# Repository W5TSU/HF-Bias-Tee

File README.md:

# HF Bias-Tee

Designed in KiCAD V9. 

This is my first attempt to design a board. I'll post some results after HF testing.

## References
- [Started as - https://github.com/zleffke/kicad_bias_tee](https://github.com/zleffke/kicad_bias_tee)
- [Reeve Observatory - Long Wavelength Array Active Crossed-Dipole Antenna](http://www.reeve.com/RadioScience/Antennas/ActiveCrossed-Dipole/LWA_Antenna.htm)
- [Long Wavelength Array (LWA) Memo Series](https://www.faculty.ece.vt.edu/swe/lwa/)
- [Bias-T Design Considerations for the LWA by Brian Hicks, Bill Erickson](https://www.faculty.ece.vt.edu/swe/lwa/memo/lwa0135.pdf)
# HF-Bias-Tee

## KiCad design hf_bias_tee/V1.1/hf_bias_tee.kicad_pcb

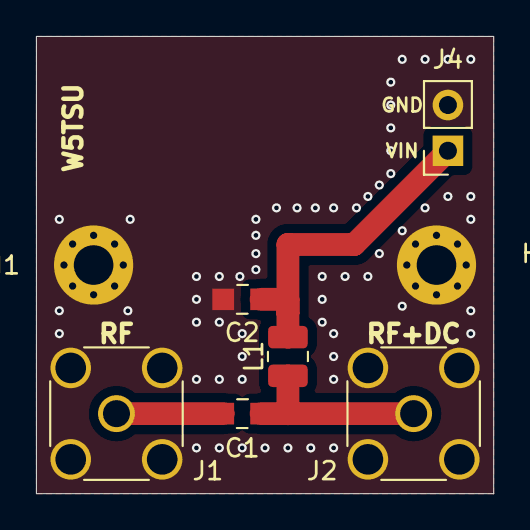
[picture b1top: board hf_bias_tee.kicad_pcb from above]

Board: 2 copper layers, 25.4 x 25.4 mm, 8 parts (0 on the bottom side), 4 nets.

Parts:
C1, C2: 0.1uF; 0805
H1, H2: MHP; MountingHole_2.2mm_M2_Pad_Via
J1: RF; SMA_Amphenol_132134_Vertical
J2: RF+DC; SMA_Amphenol_132134_Vertical
J4: DC; PinSocket_1x02_P2.54mm_Vertical
L1: 4.7uH; L_1008_2520Metric

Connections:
GND: C2.2, H1.1, H2.1, J1.2, J2.2, J4.2
unnamed: C1.1, J2.1, L1.2
unnamed: C1.2, J1.1
unnamed: C2.1, J4.1, L1.1

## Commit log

2025-05-22 Add files via upload
    First Release

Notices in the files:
hf_bias_tee/V1.1/hf_bias_tee.kicad_pcb:
creativecommons.org/licenses/by/4.0
License: CC BY 4.0
